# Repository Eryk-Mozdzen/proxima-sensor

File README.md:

# "Proxima" sensor

Simple, low cost, IR proximity sensor, designed for minisumo class robots. Operates at 56 kHz frequency. Dimensions: 12x17x15 mm.

## Projects goals
- \>20cm detection range
- 3.3/5V power supply voltage
- \<100mA power supply current
- single logic output
- smallest possible dimensions
- not operating at 38 kHz ([robot start module](https://p1r.se/startmodule/) frequency)
- plastic case
- status led

## Workflow

### Done:
- version 1.0 assembly
- raw tests
- replace resistors to compensate parasitic capacity
- tests with case

### In progress:
- searching for new square wave generator (NE555 is not suitable for aplications below 4.5V, but works)
- design better case 
	* receiver closer to front
	* add wall between receiver and transmitter led
	* add gap to improve taking out elektronics
	* increase hole diameter

### To do:
- print & test improved case

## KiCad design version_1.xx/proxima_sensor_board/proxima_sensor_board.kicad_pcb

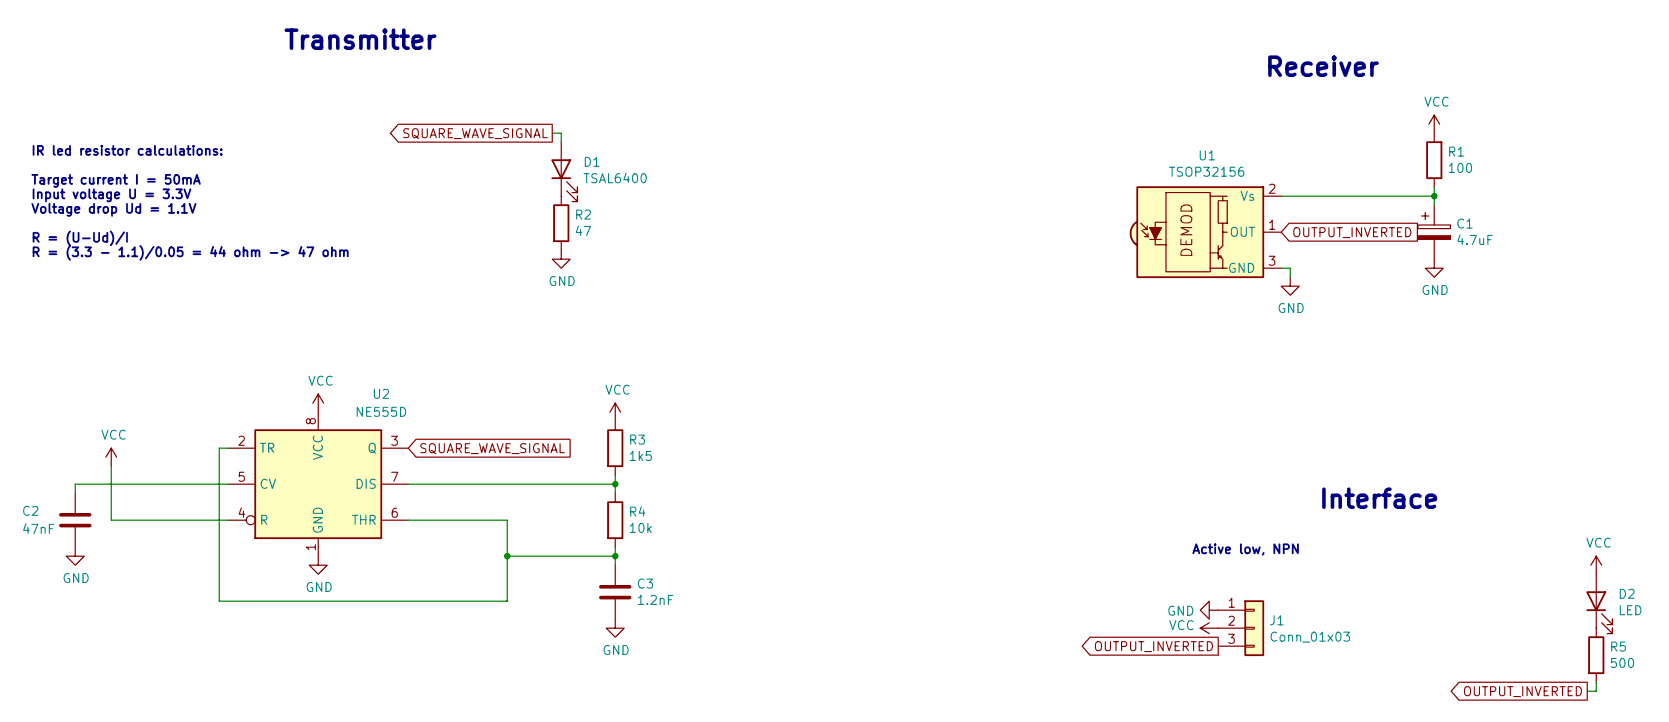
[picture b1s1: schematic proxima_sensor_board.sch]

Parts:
C1: 4.7uF; CP_EIA-3216-10_Kemet-I
C2: 47nF; C_0805_2012Metric
C3: 1.2nF; C_0805_2012Metric
D1: TSAL6400; LED_D5.0mm_IRGrey
D2: LED; LED_0805_2012Metric
J1: Conn_01x03; PinHeader_1x03_P2.54mm_Vertical
R1: 100; R_0805_2012Metric
R2: 47; R_0805_2012Metric
R3: 1k5; R_0805_2012Metric
R4: 10k; R_0805_2012Metric
R5: 500; R_0805_2012Metric
U1: TSOP32156; Vishay_MOLD-3Pin
U2: NE555D; SOIC-8_3.9x4.9mm_P1.27mm

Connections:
GND: C1.2, C2.2, C3.2, J1.1, R2.2, U1.3 (GND), U2.1 (GND)
unnamed: C1.1, R1.1, U1.2 (Vs)
unnamed: C2.1, U2.5 (CV)
unnamed: C3.1, R4.2, U2.2 (TR), U2.6 (THR)
unnamed: D1.1 (K), R2.1
unnamed: D2.1 (K), R5.1
unnamed: R3.2, R4.1, U2.7 (DIS)
OUTPUT_INVERTED: J1.3, R5.2, U1.1 (OUT)
SQUARE_WAVE_SIGNAL: D1.2 (A), U2.3 (Q)
VCC: D2.2 (A), J1.2, R1.2, R3.1, U2.4 (R), U2.8 (VCC)

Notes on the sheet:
IR led resistor calculations: Target current I = 50mA Input voltage U = 3.3V Voltage drop Ud = 1.1V R = (U-Ud)/I R = (3.3 - 1.1)/0.05 = 44 ohm -> 47 ohm
Transmitter
Receiver
Interface
Active low, NPN

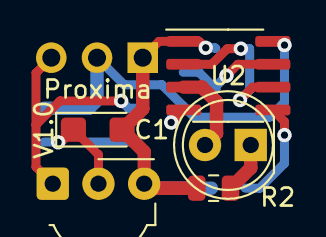
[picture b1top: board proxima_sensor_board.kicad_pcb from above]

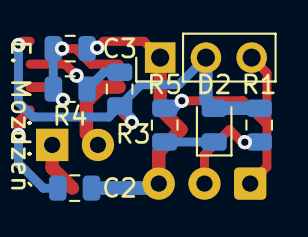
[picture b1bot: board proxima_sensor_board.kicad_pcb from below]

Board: 2 copper layers, 13 parts (8 on the bottom side), 10 nets.

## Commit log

2021-07-29 First schematic
2021-08-02 Smaller connector and version number
2021-08-02 Routes ready
2021-08-02 Create 3D model
2021-08-02 Little fillet
2021-08-14 Panelize board and gerbers
2021-08-15 Led calculations fix
2021-08-15 5mm breakway
2021-08-16 panelization 2
2021-09-13 First tests
2021-09-14 Case improvements
2022-01-19 update stl files
2022-01-29 update case
